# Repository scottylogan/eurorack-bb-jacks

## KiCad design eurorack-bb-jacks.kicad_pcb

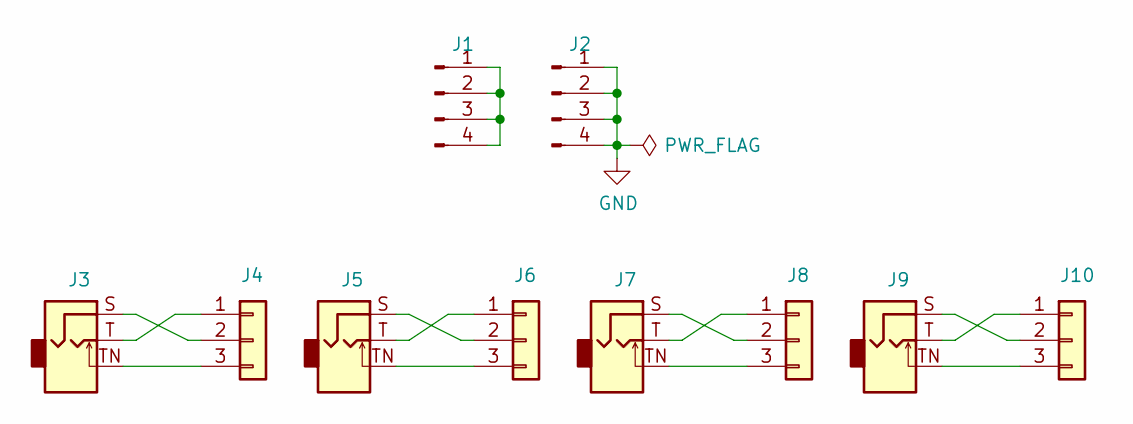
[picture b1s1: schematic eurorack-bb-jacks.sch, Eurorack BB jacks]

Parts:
J1, J2: Conn_01x04_Male; PinHeader_1x04_P2.54mm_Vertical
J3, J5, J7, J9: AudioJack2_SwitchT; Jack_3.5mm_QingPu_WQP-PJ398SM_Vertical_CircularHoles
J4, J6, J8, J10: Conn_01x03; PinSocket_1x03_P2.54mm_Vertical

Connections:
GND: J2.1, J2.2, J2.3, J2.4
unnamed: J1.1, J1.2, J1.3, J1.4
unnamed: J3.S, J4.2
unnamed: J3.T, J4.1
unnamed: J3.TN, J4.3
unnamed: J5.S, J6.2
unnamed: J5.T, J6.1
unnamed: J5.TN, J6.3
unnamed: J7.S, J8.2
unnamed: J7.T, J8.1
unnamed: J7.TN, J8.3
unnamed: J9.T, J10.1
unnamed: J9.S, J10.2
unnamed: J9.TN, J10.3

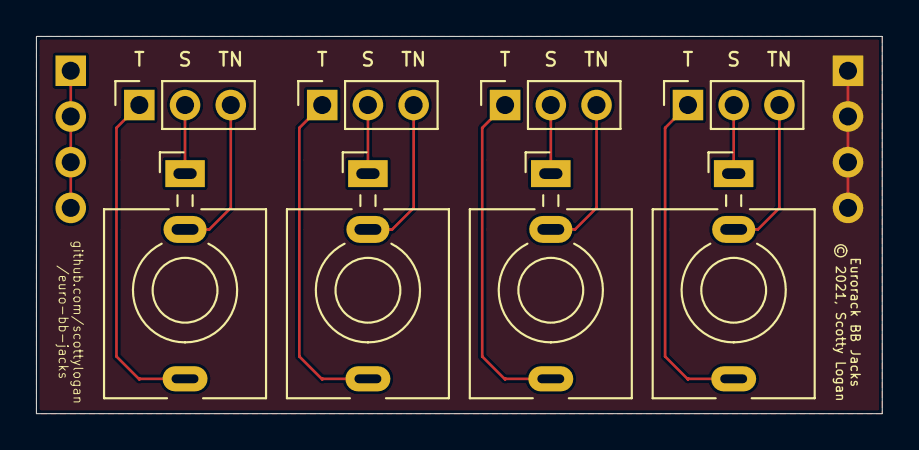
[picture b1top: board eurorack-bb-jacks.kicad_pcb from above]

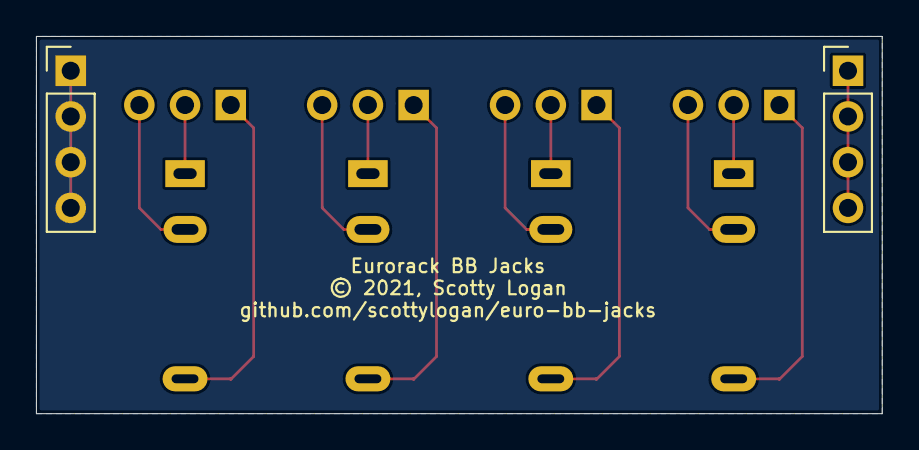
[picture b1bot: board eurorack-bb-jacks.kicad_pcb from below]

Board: 2 copper layers, 47.0 x 21.0 mm, 10 parts (2 on the bottom side), 14 nets.

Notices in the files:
eurorack-bb-jacks.kicad_pcb:
© 2021, Scotty Logan
